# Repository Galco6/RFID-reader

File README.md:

# RFID-reader
125kHz RFID reader of EM4100 protocol tags.

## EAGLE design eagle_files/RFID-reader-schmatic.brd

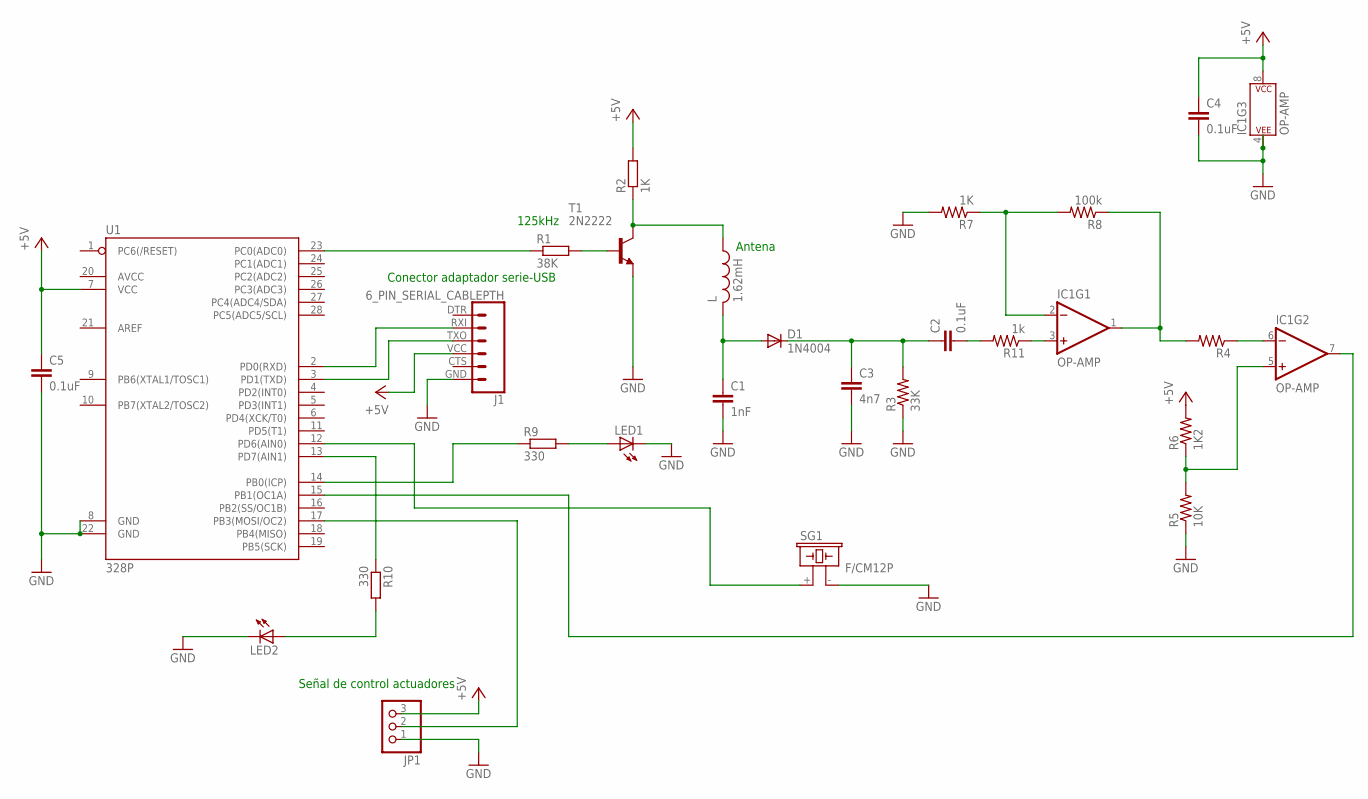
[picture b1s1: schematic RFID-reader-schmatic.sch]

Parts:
C1: 1nF; C2.5-3
C2, C4, C5: 0.1uF; C2.5-3
C3: 4n7; C2.5-3
D1: 1N4004; DO41-10
IC1: OP-AMP; DIP08
J1: 6_PIN_SERIAL_CABLEPTH; FTDI_BASIC
JP1: PINHD-1X3; 1X03
L: 1.62mH; 6000
LED1, LED2: LED3MM
R1: 38K; 0204/7
R2, R7: 1K; 0204/7
R3: 33K; 0204/7
R4: R-US_0204/7; 0204/7
R5: 10K; 0204/7
R6: 1K2; 0204/7
R8: 100k; 0204/7
R9, R10: 330; 0204/7
R11: 1k; 0204/7
SG1: F/CM12P
T1: 2N2222; TO92-EBC-OVAL
U1: 328P; DIP28

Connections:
GND: C1.2, C3.2, C4.2, C5.2, IC1.4 (P$V-), J1.GND (6), JP1.1, LED1.K (C), LED2.K (C), R3.1, R5.1, R7.2, SG1.- (2), T1.E, U1.8 (GND), U1.22 (GND)
unnamed: R10.1, U1.13 (PD7(AIN1))
unnamed: L.1, R2.1, T1.C
unnamed: R1.2, T1.B
unnamed: R1.1, U1.23 (PC0(ADC0))
unnamed: C1.1, D1.A, L.2
unnamed: IC1.6 (-IN), R4.1
unnamed: R9.1, U1.14 (PB0(ICP))
unnamed: C2.1, C3.1, D1.C, R3.2
unnamed: IC1.7 (OUT), U1.15 (PB1(OC1A))
unnamed: IC1.5 (+IN), R5.2, R6.1
unnamed: C4.1, IC1.8 (P$V+)
unnamed: C2.2, R11.2
unnamed: IC1.1 (OUT), R4.2, R8.1
unnamed: IC1.2 (-IN), R7.1, R8.2
unnamed: SG1.+ (1), U1.12 (PD6(AIN0))
unnamed: LED1.A, R9.2
unnamed: JP1.2, U1.17 (PB3(MOSI/OC2))
unnamed: J1.RXI (2), U1.2 (PD0(RXD))
unnamed: J1.TXO (3), U1.3 (PD1(TXD))
unnamed: LED2.A, R10.2
unnamed: IC1.3 (+IN), R11.1
VCC: C5.1, J1.VCC (4), JP1.3, R2.2, R6.2, U1.7 (VCC)

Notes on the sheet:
125kHz
Conector adaptador serie-USB
Señal de control actuadores
Antena

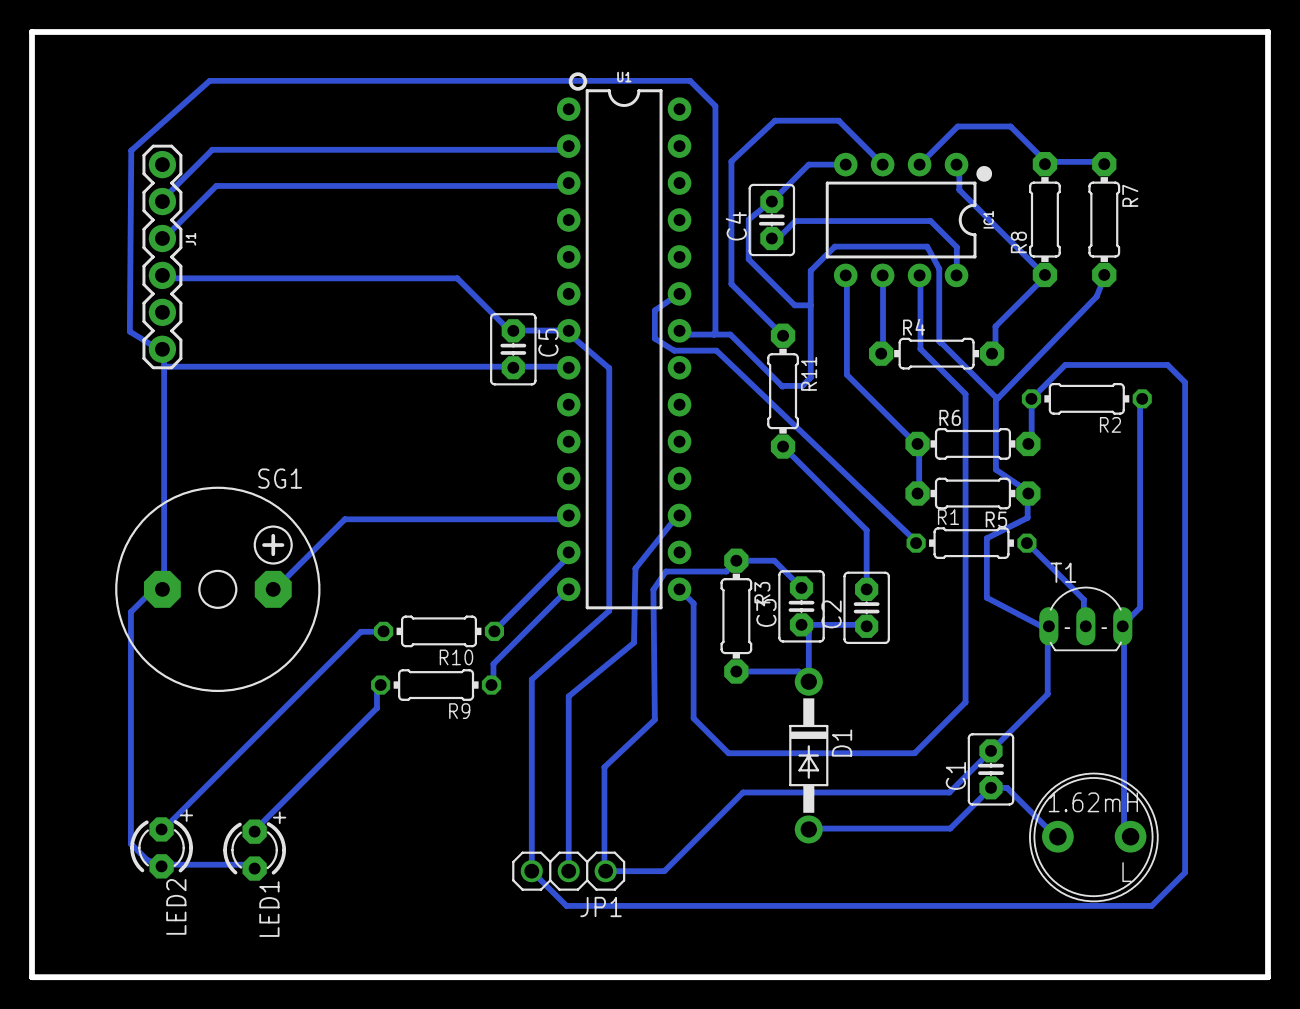
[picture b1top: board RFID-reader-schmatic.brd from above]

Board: 2 copper layers, 85.0 x 65.0 mm, 26 parts (0 on the bottom side), 23 nets.

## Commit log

2017-12-09 Add images
2018-02-22 Eagle files
2018-04-11 Added PDF files
2020-05-10 Added simulation files

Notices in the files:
parts and their libraries:
SparkFun-Connectors: Licensing: Creative Commons ShareAlike 4.0 International - https://creativecommons.org/licenses/by-sa/4.0
